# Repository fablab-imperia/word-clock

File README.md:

<!-- PROJECT LOGO -->
<br />
<div align="center">

  <h3 align="center">Word Clock</h3>

  <p align="center">
    This repository contains the software and hardware components (KiKad files)
    used by <a href="https://www.fablabimperia.org"> Fablab Imperia </a> to build its amazing Word Clock! 
  </p>
</div>

<!-- TABLE OF CONTENTS -->
<details>
  <summary>Table of Contents</summary>
  <ol>
    <li>
      <a href="#about-the-project">About The Project</a>
      <ul>
        <li><a href="#built-with">Built With</a></li>
      </ul>
    </li>
    <li>
      <a href="#getting-started">Getting Started</a>
      <ul>
        <li><a href="#prerequisites">Prerequisites</a></li>
        <li><a href="#installation">Installation</a></li>
      </ul>
    </li>
    <li><a href="#usage">Usage</a></li>
    <li><a href="#roadmap">Roadmap</a></li>
    <li><a href="#contributing">Contributing</a></li>
    <li><a href="#license">License</a></li>
    <li><a href="#contact">Contact</a></li>
    <li><a href="#acknowledgments">Acknowledgments</a></li>
  </ol>
</details>

<!-- ABOUT THE PROJECT -->
## About The Project

A word clock is a device that shows the current time on a LED matrix by using the word rapresentation of the actual time in a specific language and with a specific frequency.

For simplicity we chose to use a 12 x 12 matrix of letters, Italian as a language and 5 minutes as a frequency.
So time is shown using Italian sentences every 5 minutes.
Due to the simplicity and flexibility of the solution, it can be adapted to other languages and frequencies.

You are free to fork this project and use it as a base for your own implementations.

<p align="right">(<a href="#readme-top">back to top</a>)</p>

<!-- GETTING STARTED -->
## Getting Started

### Bill of materials

* 1 Arduino Mini
* 

### Prerequisites

This is an example of how to list things you need to use the software and how to install them.
* npm
  ```sh
  npm install npm@latest -g
  ```

### Installation

_Below is an example of how you can instruct your audience on installing and setting up your app. This template doesn't rely on any external dependencies or services._

1. Get a free API Key at [https://example.com](https://example.com)
2. Clone the repo
   ```sh
   git clone https://github.com/your_username_/Project-Name.git
   ```
3. Install NPM packages
   ```sh
   npm install
   ```
4. Enter your API in `config.js`
   ```js
   const API_KEY = 'ENTER YOUR API';
   ```

<p align="right">(<a href="#readme-top">back to top</a>)</p>

<!-- USAGE EXAMPLES -->
## Usage

Use this space to show useful examples of how a project can be used. Additional screenshots, code examples and demos work well in this space. You may also link to more resources.

_For more examples, please refer to the [Documentation](https://example.com)_

<p align="right">(<a href="#readme-top">back to top</a>)</p>

<!-- ROADMAP -->
## Roadmap

- [x] Add Changelog
- [x] Add back to top links
- [ ] Add Additional Templates w/ Examples
- [ ] Add "components" document to easily copy & paste sections of the readme
- [ ] Multi-language Support
    - [ ] Chinese
    - [ ] Spanish

See the [open issues](https://github.com/othneildrew/Best-README-Template/issues) for a full list of proposed features (and known issues).

<p align="right">(<a href="#readme-top">back to top</a>)</p>

<!-- CONTRIBUTING -->
## Contributing

Contributions are what make the open source community such an amazing place to learn, inspire, and create. Any contributions you make are **greatly appreciated**.

If you have a suggestion that would make this better, please fork the repo and create a pull request. You can also simply open an issue with the tag "enhancement".
Don't forget to give the project a star! Thanks again!

1. Fork the Project
2. Create your Feature Branch (`git checkout -b feature/AmazingFeature`)
3. Commit your Changes (`git commit -m 'Add some AmazingFeature'`)
4. Push to the Branch (`git push origin feature/AmazingFeature`)
5. Open a Pull Request

<p align="right">(<a href="#readme-top">back to top</a>)</p>

<!-- LICENSE -->
## License

Distributed under the MIT License. See `LICENSE.txt` for more information.

<p align="right">(<a href="#readme-top">back to top</a>)</p>

<!-- CONTACT -->
## Contact

Your Name - [@your_twitter](https://twitter.com/your_username) - email@example.com

Project Link: [https://github.com/your_username/repo_name](https://github.com/your_username/repo_name)

<p align="right">(<a href="#readme-top">back to top</a>)</p>

<!-- ACKNOWLEDGMENTS -->
## Acknowledgments

Use this space to list resources you find helpful and would like to give credit to. I've included a few of my favorites to kick things off!

* [Choose an Open Source License](https://choosealicense.com)
* [GitHub Emoji Cheat Sheet](https://www.webpagefx.com/tools/emoji-cheat-sheet)
* [Malven's Flexbox Cheatsheet](https://flexbox.malven.co/)
* [Malven's Grid Cheatsheet](https://grid.malven.co/)
* [Img Shields](https://shields.io)
* [GitHub Pages](https://pages.github.com)
* [Font Awesome](https://fontawesome.com)
* [React Icons](https://react-icons.github.io/react-icons/search)

<p align="right">(<a href="#readme-top">back to top</a>)</p>

<!-- MARKDOWN LINKS & IMAGES -->
<!-- https://www.markdownguide.org/basic-syntax/#reference-style-links -->
[contributors-shield]: https://img.shields.io/github/contributors/othneildrew/Best-README-Template.svg?style=for-the-badge
[contributors-url]: https://github.com/othneildrew/Best-README-Template/graphs/contributors
[forks-shield]: https://img.shields.io/github/forks/othneildrew/Best-README-Template.svg?style=for-the-badge
[forks-url]: https://github.com/othneildrew/Best-README-Template/network/members
[stars-shield]: https://img.shields.io/github/stars/othneildrew/Best-README-Template.svg?style=for-the-badge
[stars-url]: https://github.com/othneildrew/Best-README-Template/stargazers
[issues-shield]: https://img.shields.io/github/issues/othneildrew/Best-README-Template.svg?style=for-the-badge
[issues-url]: https://github.com/othneildrew/Best-README-Template/issues
[license-shield]: https://img.shields.io/github/license/othneildrew/Best-README-Template.svg?style=for-the-badge
[license-url]: https://github.com/othneildrew/Best-README-Template/blob/master/LICENSE.txt
[linkedin-shield]: https://img.shields.io/badge/-LinkedIn-black.svg?style=for-the-badge&logo=linkedin&colorB=555
[linkedin-url]: https://linkedin.com/in/othneildrew
[product-screenshot]: images/screenshot.png
[Next.js]: https://img.shields.io/badge/next.js-000000?style=for-the-badge&logo=nextdotjs&logoColor=white
[Next-url]: https://nextjs.org/
[React.js]: https://img.shields.io/badge/React-20232A?style=for-the-badge&logo=react&logoColor=61DAFB
[React-url]: https://reactjs.org/
[Vue.js]: https://img.shields.io/badge/Vue.js-35495E?style=for-the-badge&logo=vuedotjs&logoColor=4FC08D
[Vue-url]: https://vuejs.org/
[Angular.io]: https://img.shields.io/badge/Angular-DD0031?style=for-the-badge&logo=angular&logoColor=white
[Angular-url]: https://angular.io/
[Svelte.dev]: https://img.shields.io/badge/Svelte-4A4A55?style=for-the-badge&logo=svelte&logoColor=FF3E00
[Svelte-url]: https://svelte.dev/
[Laravel.com]: https://img.shields.io/badge/Laravel-FF2D20?style=for-the-badge&logo=laravel&logoColor=white
[Laravel-url]: https://laravel.com
[Bootstrap.com]: https://img.shields.io/badge/Bootstrap-563D7C?style=for-the-badge&logo=bootstrap&logoColor=white
[Bootstrap-url]: https://getbootstrap.com
[JQuery.com]: https://img.shields.io/badge/jQuery-0769AD?style=for-the-badge&logo=jquery&logoColor=white
[JQuery-url]: https://jquery.com

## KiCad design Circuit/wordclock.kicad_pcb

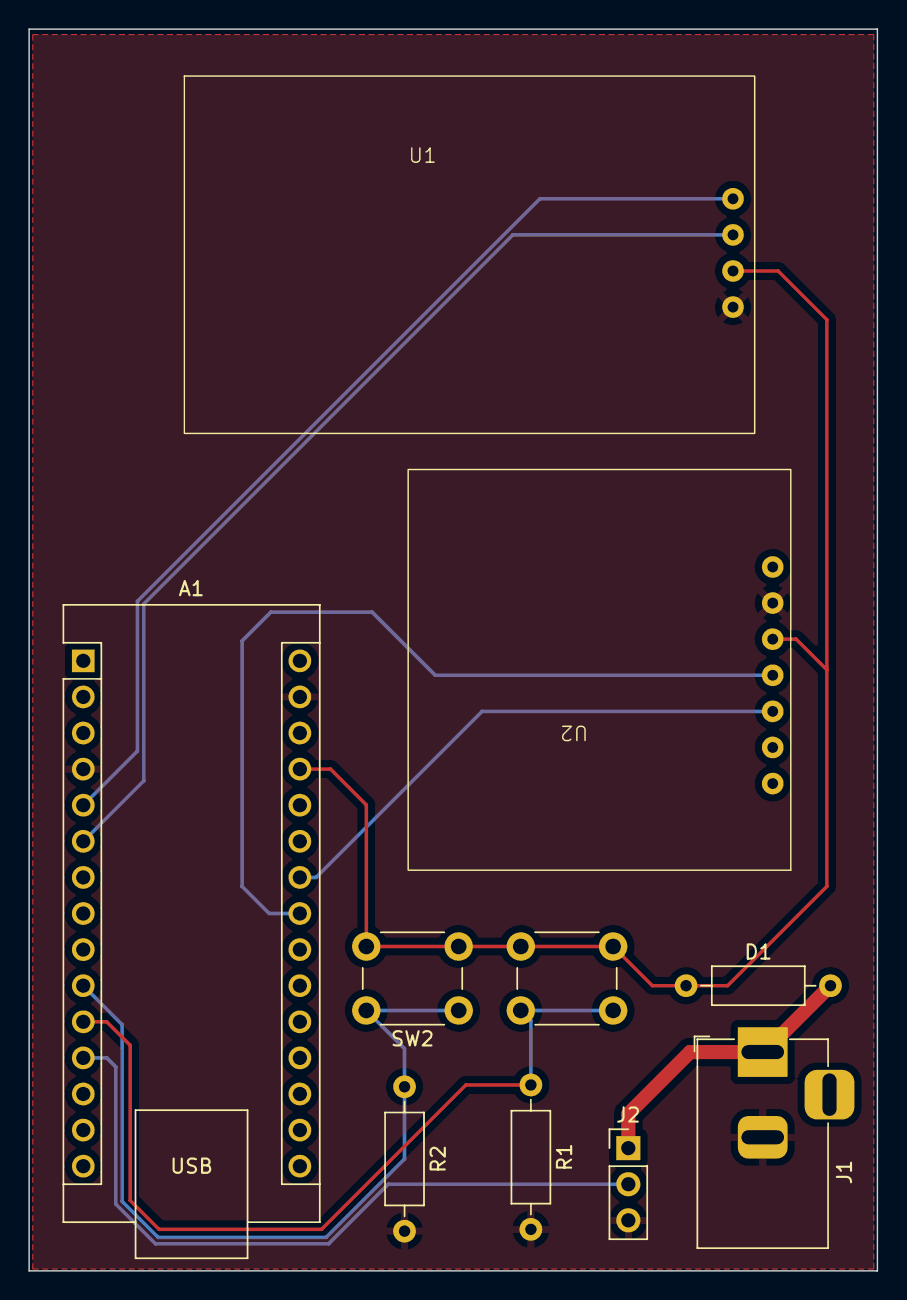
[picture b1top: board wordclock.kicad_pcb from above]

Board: 2 copper layers, 59.7 x 87.4 mm, 10 parts (0 on the bottom side), 10 nets.

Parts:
A1: Arduino_Nano_v3.x; Arduino_Nano
D1: D_Schottky; R_Axial_DIN0207_L6.3mm_D2.5mm_P10.16mm_Horizontal
J1: Conn_Coaxial_Power; BarrelJack_Horizontal
J2: Conn_01x03_Pin; PinHeader_1x03_P2.54mm_Vertical
R1, R2: R; R_Axial_DIN0207_L6.3mm_D2.5mm_P10.16mm_Horizontal
SW1: MIN; SW_PUSH_6mm
SW2: ORE; SW_PUSH_6mm
U1: TM1637
U2: RTC

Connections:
+5V: A1.27 (+5V), D1.1 (K), SW1.2, SW2.2, U1.2 (VCC), U2.3 (VCC)
+5VP: D1.2 (A), J1.1 (In), J2.1
GND: A1.4 (GND), A1.29 (GND), J1.2 (Ext), J2.3, R1.2, R2.2, U1.1 (GND), U2.2 (GND)
unnamed: A1.23 (A4), U2.4 (SDA)
unnamed: A1.24 (A5), U2.5 (SCL)
unnamed: A1.5 (D2), U1.4 (CK)
unnamed: A1.6 (D3), U1.3 (DIO)
unnamed: A1.10 (D7), R2.1, SW2.1
unnamed: A1.11 (D8), R1.1, SW1.1
unnamed: A1.12 (D9), J2.2

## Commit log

2023-04-15 prima versione progetto
2023-04-22 new version with all words stored
2023-04-22 prima versione con generazione ore
2023-04-22 still incomplete
2023-04-23 fixed issues
2023-04-28 more fixes
2023-04-29 nuova versione
2023-04-29 aggiornamenti
2023-04-30 last version with liquid crystal
2023-05-01 added button support for time settings
2023-05-07 added library for 7 segments display with 4 digits
2023-05-07 last fixes
2023-05-09 versione finale
2023-05-09 version final
2023-05-25 pullup resistor option fixed
2023-06-25 aggiunta progetto hardware con Kikad prima versione
2023-06-25 Aggiunto template per il progetto
2023-06-25 aggiunte immagini schema e PCB
2023-06-25 rimosse parti inutili
2023-07-15 iniziata versione inglese documentazione progetto
